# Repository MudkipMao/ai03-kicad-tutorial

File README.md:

# ai03-kicad-tutorial
Following ai03's KiCad guide here: https://wiki.ai03.me/books/pcb-design/chapter/pcb-designer-guide

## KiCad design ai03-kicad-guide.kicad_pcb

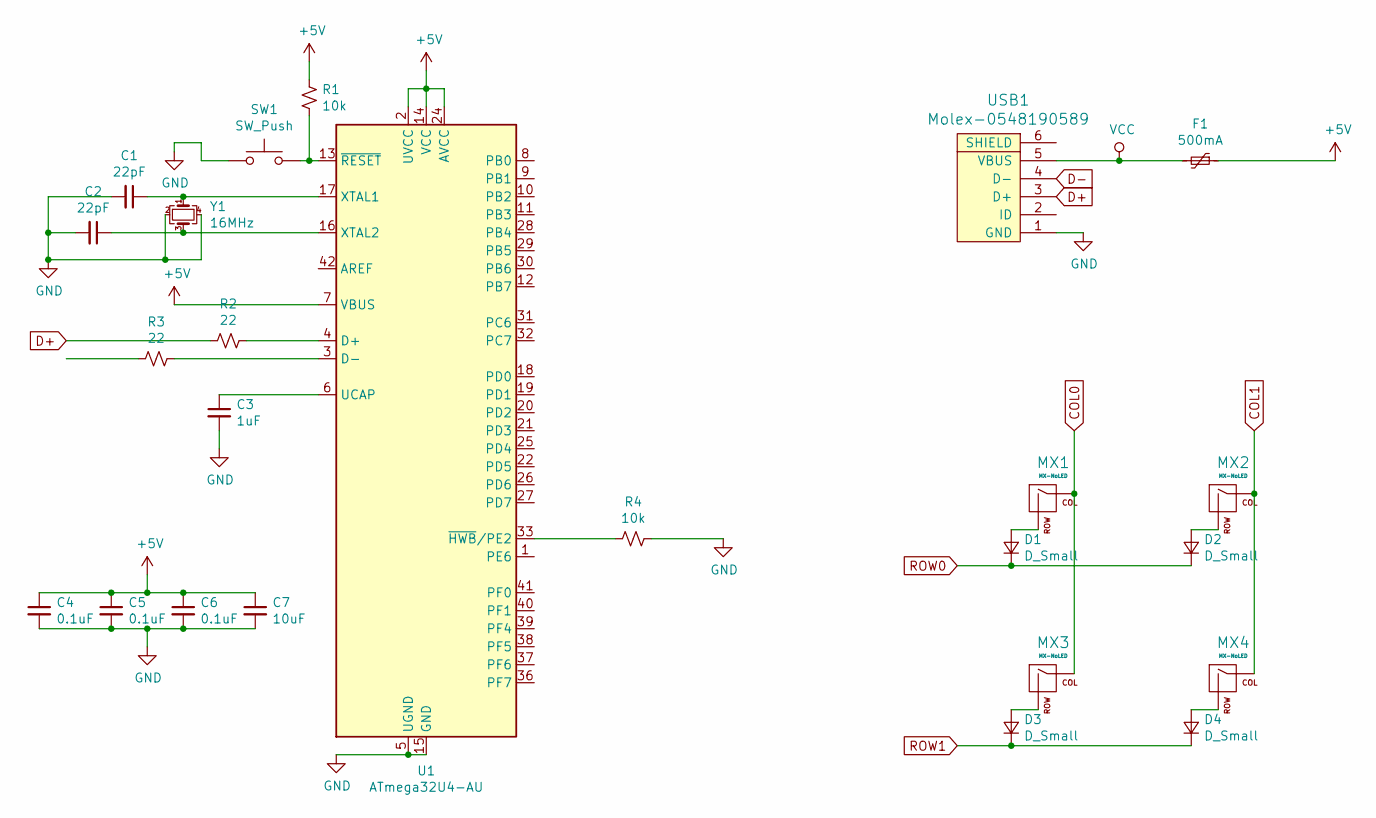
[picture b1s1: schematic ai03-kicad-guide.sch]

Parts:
C1, C2: 22pF; C_0805_2012Metric
C3: 1uF; C_0805_2012Metric
C4, C5, C6: 0.1uF; C_0805_2012Metric
C7: 10uF; C_0805_2012Metric
D1, D2, D3, D4: D_Small; D_0805_2012Metric
F1: 500mA; Fuse_0805_2012Metric
MX1, MX2, MX3: MX-NoLED; MX-1U-NoLED
MX4: MX-NoLED; R_0805_2012Metric
R1, R4: 10k; R_0805_2012Metric
R2, R3: 22; R_0805_2012Metric
SW1: SW_Push; SKQG-1155865
U1: ATmega32U4-AU; TQFP-44_10x10mm_P0.8mm
USB1: Molex-0548190589
Y1: 16MHz; Crystal_SMD_3225-4Pin_3.2x2.5mm

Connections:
+5V: C4.1, C5.1, C6.1, C7.1, F1.1, R1.1, U1.2 (UVCC), U1.7 (VBUS), U1.14 (VCC), U1.24 (AVCC), U1.34 (VCC), U1.44 (AVCC)
COL0: MX1.1 (COL), MX3.1 (COL)
COL1: MX2.1 (COL), MX4.1 (COL)
D+: R2.2, USB1.3 (D+)
D-: USB1.4 (D-)
GND: C1.2, C2.2, C3.2, C4.2, C5.2, C6.2, C7.2, R4.1, SW1.1, U1.5 (UGND), U1.15 (GND), U1.23 (GND), U1.35 (GND), U1.43 (GND), USB1.1 (GND), Y1.2, Y1.4
unnamed: C1.1, U1.17 (XTAL1), Y1.1
unnamed: C2.1, U1.16 (XTAL2), Y1.3
unnamed: C3.1, U1.6 (UCAP)
unnamed: D1.2 (A), MX1.2 (ROW)
unnamed: D2.2 (A), MX2.2 (ROW)
unnamed: D3.2 (A), MX3.2 (ROW)
unnamed: D4.2 (A), MX4.2 (ROW)
unnamed: R1.2, SW1.2, U1.13 (~RESET)
unnamed: R2.1, U1.4 (D+)
unnamed: R3.1, U1.3 (D-)
unnamed: R4.2, U1.33 (~HWB~/PE2)
ROW0: D1.1 (K), D2.1 (K)
ROW1: D3.1 (K), D4.1 (K)
VCC: F1.2, USB1.5 (VBUS)

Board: 2 copper layers, 24 parts (7 on the bottom side), 19 nets, no tracks yet.

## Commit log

2020-05-07 Adding initial KiCad project files
2020-05-07 Added ai03 library submodules
2020-05-07 Added project specific symbol and footprint libraries
2020-05-07 Finished the MCU schematic
2020-05-07 Added all component annotations and footprints
2020-05-08 Finished with tutorial
